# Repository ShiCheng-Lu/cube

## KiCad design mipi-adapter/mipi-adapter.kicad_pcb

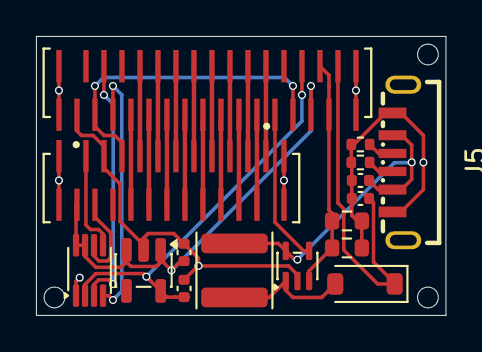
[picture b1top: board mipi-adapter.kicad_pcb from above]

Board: 4 copper layers, 22.8 x 15.5 mm, 16 parts (0 on the bottom side), 32 nets.

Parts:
C1, C2, C3, C4: 1uF; C_0402_1005Metric
D1: D_Schottky; D_SOD-123
J1: Connector; HRS_TF38-22S-0.5SV_830_
J4: Conn_01x30_Socket; HRS_TF38-30S-0.5SV_830_
J5: USB_C_Receptacle_PowerOnly_6P; USB-C-SMD_TYPE-C--015
L1: 10uH; L_APV_ANR4012
R1, R2: 5.1; R_0603_1608Metric
R3, R4: 5.1k; R_0402_1005Metric
U1: TPS61169; SOT-353_SC-70-5
U2: PCA9306; VSSOP-8_2.3x2mm_P0.5mm
U3: TPS7A2018; SOT-23-5

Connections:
unnamed: D1.2 (A), L1.1, U1.1 (SW)
unnamed: C4.1, D1.1 (K), J4.30
unnamed: J1.9 (CLKN), J4.14
unnamed: J1.8 (CLKP), J4.15
unnamed: J1.3 (D0N), J4.20
unnamed: J1.2 (D0P), J4.21
unnamed: J1.6 (D1N), J4.17
unnamed: J1.5 (D1P), J4.18
unnamed: J1.12 (D2N), J4.11
unnamed: J1.11 (D2P), J4.12
unnamed: J1.15 (D3N), J4.8
unnamed: J1.14 (D3P), J4.9
unnamed: J1.17 (PWR_EN), J4.3, J4.25
unnamed: J1.20 (SCL), U2.6 (SCL2)
unnamed: J1.21 (SDA), U2.5 (SDA2)
unnamed: J1.SH (SHIELD), J4.SH (SHIELD), J5.SH (SHIELD)
unnamed: C1.2, J1.22 (VCC), J4.27, U2.7 (VREF2), U2.8 (EN), U3.1 (IN), U3.3 (EN)
unnamed: C1.1, C2.1, C3.2, C4.2, J1.19 (GND), J4.1, J5.A12 (GND), J5.B12 (GND), R1.2, R2.2, R3.1, R4.1, U1.2 (GND), U2.1 (GND), U3.2 (GND)
unnamed: J4.4, U2.3 (SCL1)
unnamed: J4.5, U2.4 (SDA1)
unnamed: J1.16 (GND), J4.7
unnamed: J1.13 (GND), J4.10
unnamed: J1.10 (GND), J4.13
unnamed: J1.7 (GND), J4.16
unnamed: J1.4 (GND), J4.19
unnamed: J1.1 (GND), J4.22
unnamed: J4.23, U1.4 (EN)
unnamed: C2.2, J4.26, U2.2 (VREF1), U3.5 (OUT)
unnamed: J4.28, J4.29, R1.1, R2.1, U1.3 (FB)
unnamed: J5.A5 (CC1), R3.2
unnamed: J5.B5 (CC2), R4.2
unnamed: C3.1, J5.A9 (VBUS), J5.B9 (VBUS), L1.2, U1.5 (VIN)

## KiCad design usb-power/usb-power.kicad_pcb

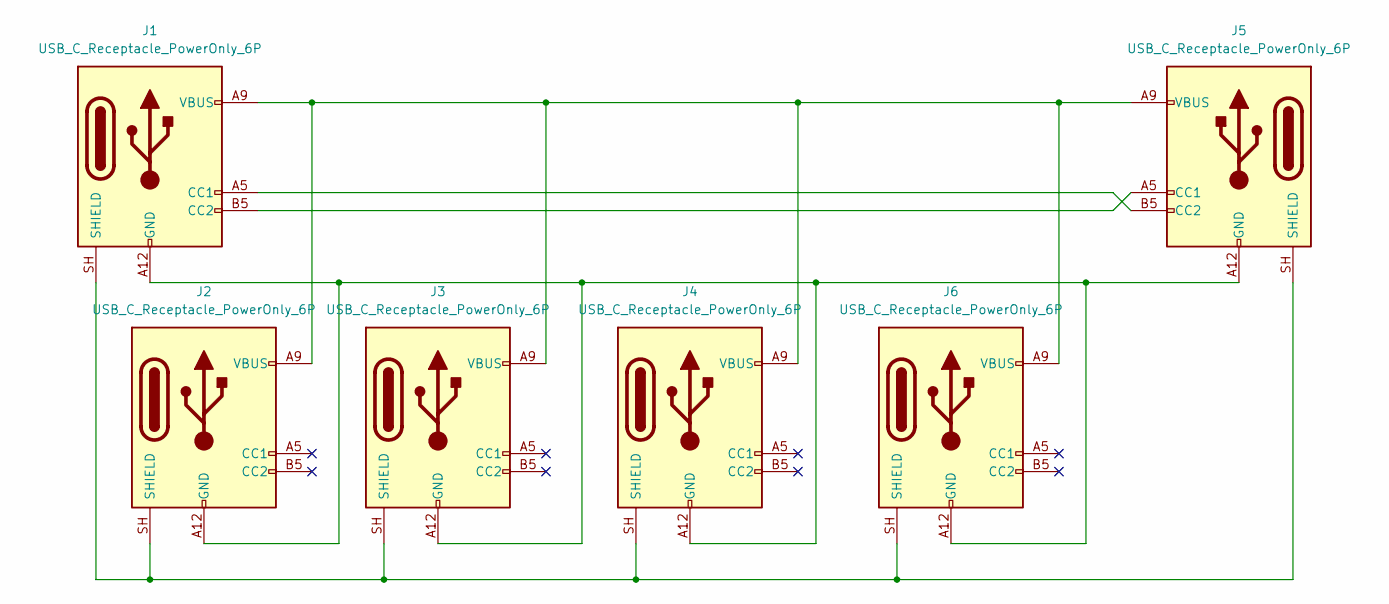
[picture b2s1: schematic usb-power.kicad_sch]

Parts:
J1, J2, J3, J4, J5, J6: USB_C_Receptacle_PowerOnly_6P; USB_C_Receptacle_GCT_USB4125-xx-x_6P_TopMnt_Horizontal

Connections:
unnamed: J1.A5 (CC1), J5.B5 (CC2)
unnamed: J1.B5 (CC2), J5.A5 (CC1)
unnamed: J1.A12 (GND), J1.B12 (GND), J2.A12 (GND), J2.B12 (GND), J3.A12 (GND), J3.B12 (GND), J4.A12 (GND), J4.B12 (GND), J5.A12 (GND), J5.B12 (GND), J6.A12 (GND), J6.B12 (GND)
unnamed: J1.SH (SHIELD), J2.SH (SHIELD), J3.SH (SHIELD), J4.SH (SHIELD), J5.SH (SHIELD), J6.SH (SHIELD)
unnamed: J1.A9 (VBUS), J1.B9 (VBUS), J2.A9 (VBUS), J2.B9 (VBUS), J3.A9 (VBUS), J3.B9 (VBUS), J4.A9 (VBUS), J4.B9 (VBUS), J5.A9 (VBUS), J5.B9 (VBUS), J6.A9 (VBUS), J6.B9 (VBUS)

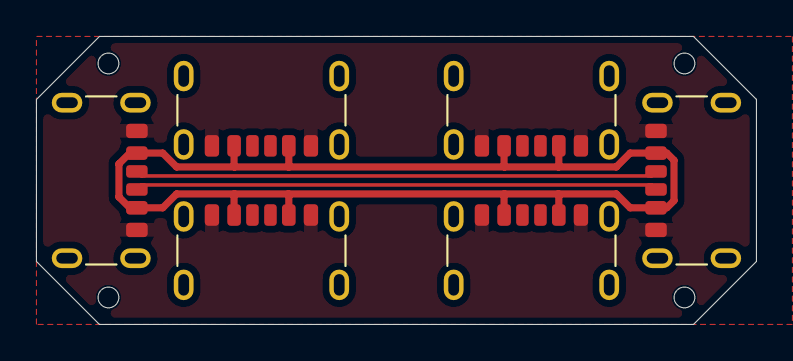
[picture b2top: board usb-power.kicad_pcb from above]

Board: 2 copper layers, 40.0 x 16.0 mm, 6 parts (0 on the bottom side), 5 nets.
